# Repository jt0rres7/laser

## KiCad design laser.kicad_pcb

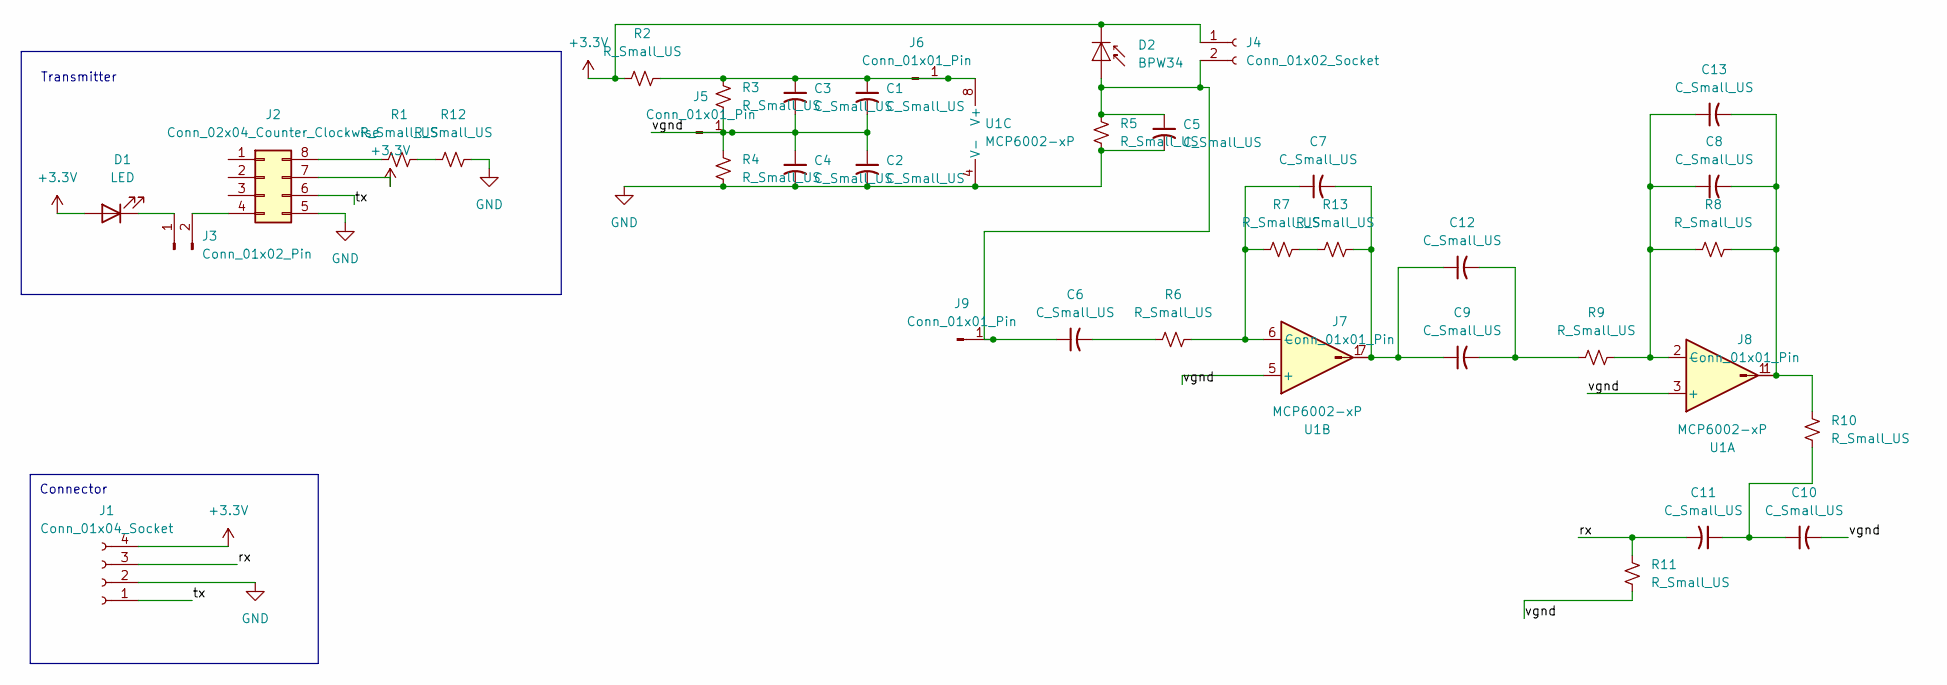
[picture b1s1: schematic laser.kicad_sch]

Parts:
C1, C2: C_Small_US; CP_Radial_D8.0mm_P3.50mm
C3, C4, C5, C6, C7, C8, C9, C10, C11, C12, C13: C_Small_US; C_Disc_D10.0mm_W2.5mm_P5.00mm
D1: LED; LED_D3.0mm
D2: BPW34; Osram_DIL2_4.3x4.65mm_P5.08mm
J1: Conn_01x04_Socket; PinSocket_1x04_P2.54mm_Vertical
J2: Conn_02x04_Counter_Clockwise; DIP-8_W7.62mm
J3: Conn_01x02_Pin; PinHeader_1x02_P2.54mm_Vertical
J4: Conn_01x02_Socket; JST_PH_B2B-PH-K_1x02_P2.00mm_Vertical
J5, J6, J7, J8, J9: Conn_01x01_Pin; PinHeader_1x01_P2.54mm_Vertical
R1, R2, R3, R4, R5, R6, R7, R8, R9, R10, R11, R12, R13: R_Small_US; R_Axial_DIN0207_L6.3mm_D2.5mm_P7.62mm_Horizontal
U1: MCP6002-xP; DIP-8_W7.62mm

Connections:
+3.3V: D1.2 (A), D2.1 (K), J1.4, J2.7, J4.1, R2.1
/rx: C11.2, J1.3, R11.1
/tx: J1.1, J2.6
/vgnd: C1.2, C2.1, C3.2, C4.1, C10.2, J5.1 (Pin_1_1), R3.1, R4.2, R11.2, U1.3 (+), U1.5 (+)
GND: C2.2, C4.2, C5.2, J1.2, J2.5, R4.1, R5.1, R12.2, U1.4 (V-)
unnamed: C6.2, R6.2
unnamed: C10.1, C11.1, R10.1
unnamed: C9.2, C12.2, R9.2
unnamed: D1.1 (K), J3.1
unnamed: C5.1, C6.1, D2.2 (A), J4.2, J9.1 (Pin_1_1), R5.2
unnamed: J2.4, J3.2
unnamed: J2.8, R1.1
unnamed: C1.1, C3.1, J6.1 (Pin_1_1), R2.2, R3.2, U1.8 (V+)
unnamed: C7.2, C9.1, C12.1, J7.1 (Pin_1_1), R13.2, U1.7
unnamed: C8.2, C13.2, J8.1 (Pin_1_1), R8.1, R10.2, U1.1
unnamed: R1.2, R12.1
unnamed: R7.1, R13.1
unnamed: C8.1, C13.1, R8.2, R9.1, U1.2 (-)
unnamed: C7.1, R6.1, R7.2, U1.6 (-)

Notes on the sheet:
Transmitter
Connector

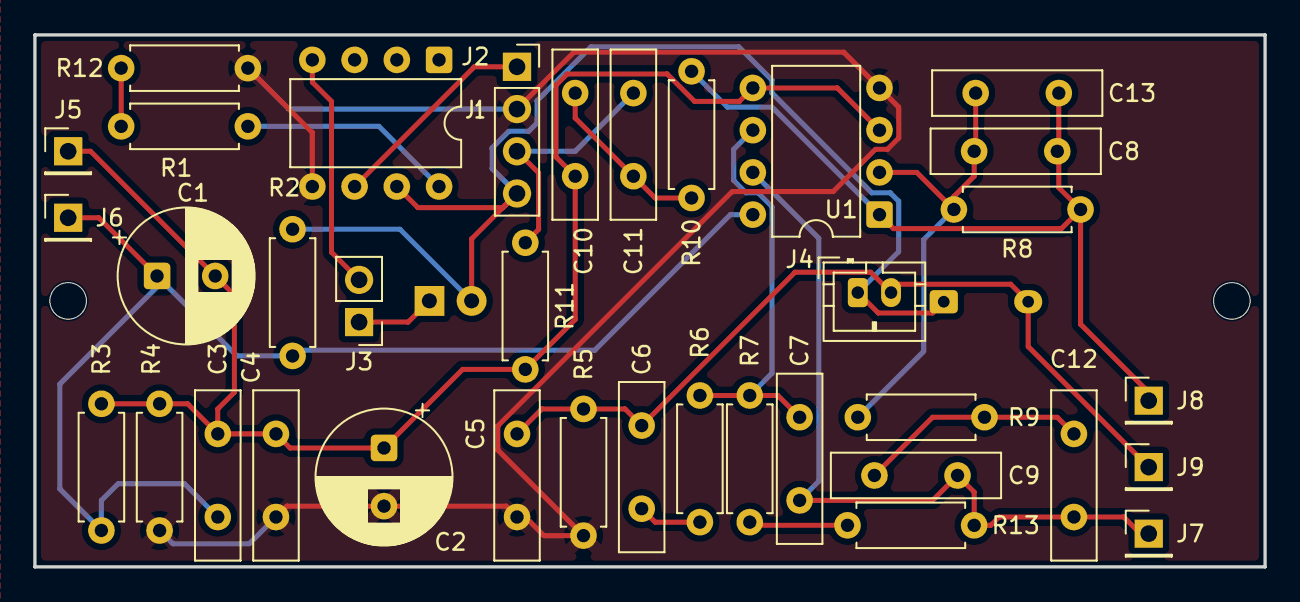
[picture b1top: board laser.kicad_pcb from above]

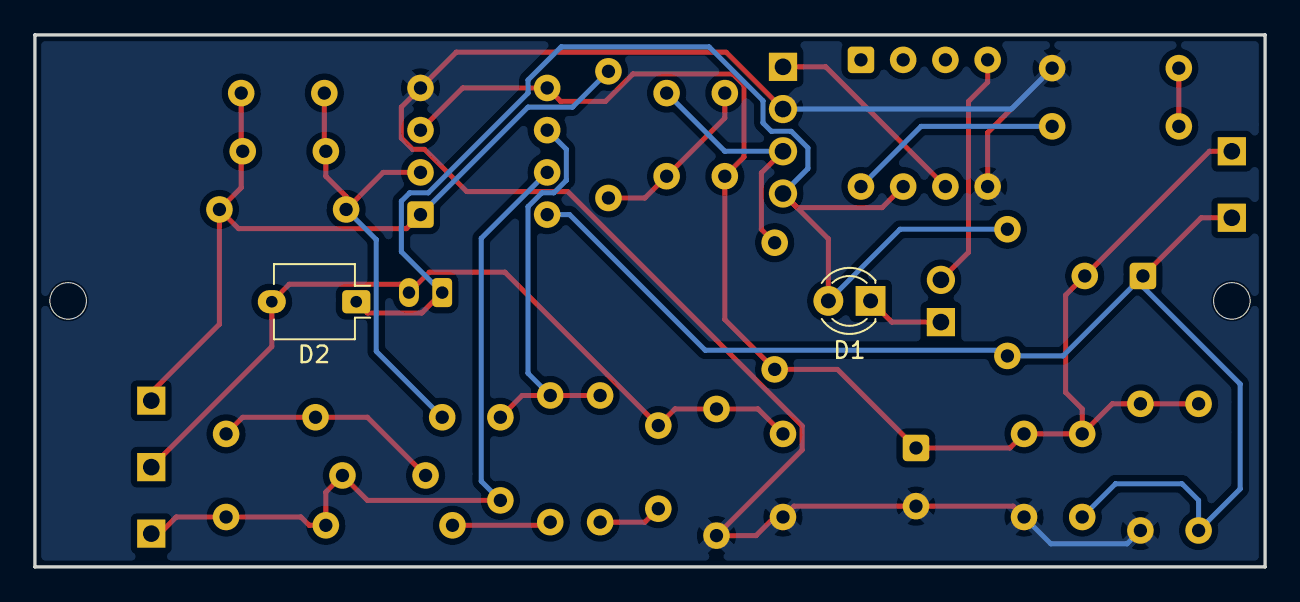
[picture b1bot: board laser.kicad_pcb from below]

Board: 2 copper layers, 74.0 x 32.0 mm, 38 parts (2 on the bottom side), 19 nets.
